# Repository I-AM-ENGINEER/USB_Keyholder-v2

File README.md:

# USB_Keyholder
 Compact USB password manager with battery and oled display

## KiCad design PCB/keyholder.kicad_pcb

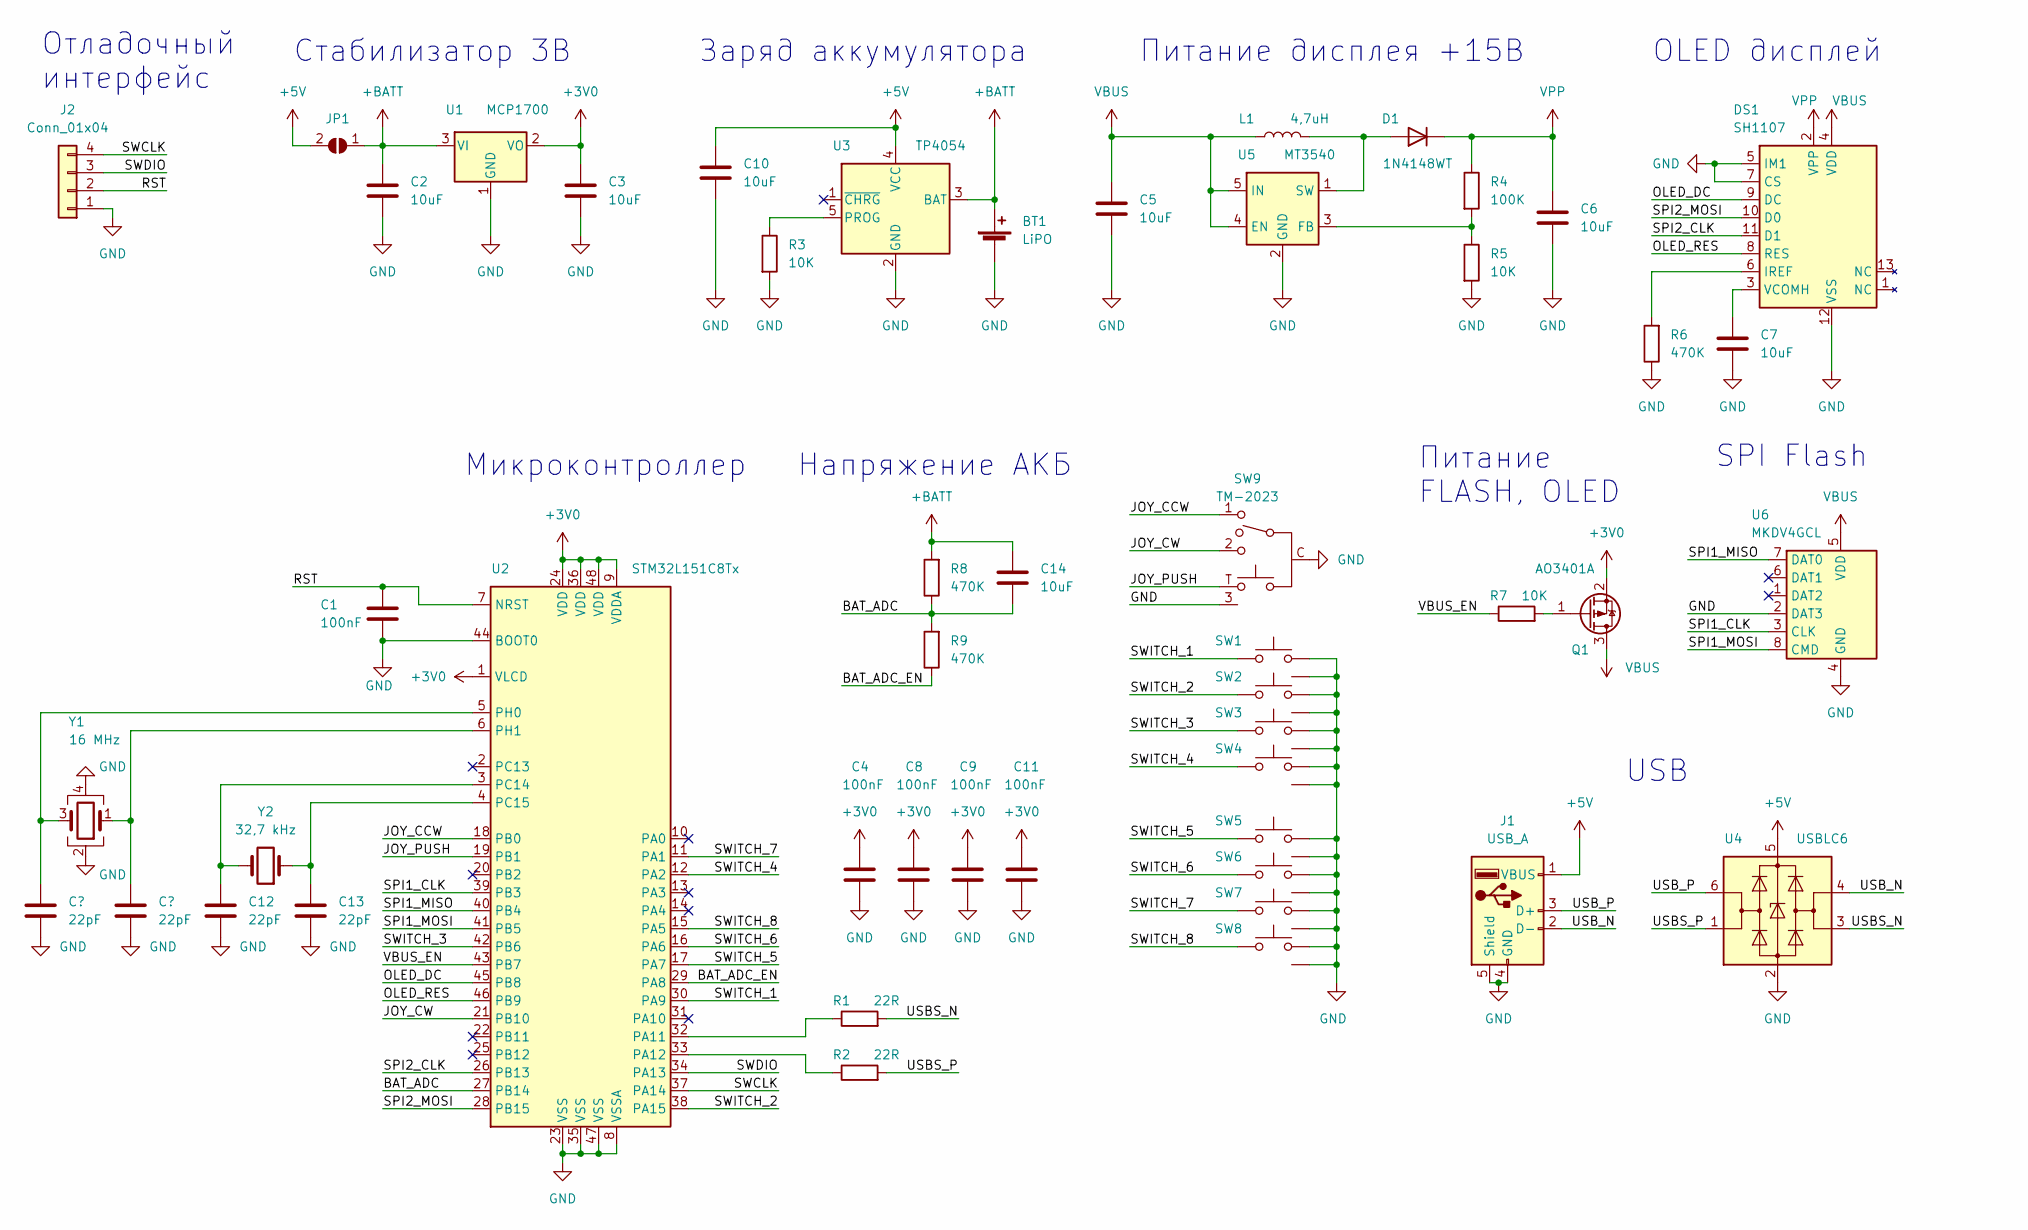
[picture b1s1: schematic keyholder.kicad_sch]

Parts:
BT1: LiPO; PinHeader_1x02_P2.00mm_Vertical
C1, C4, C8, C9, C11: 100nF; C_0603_1608Metric
C2, C3, C5, C6, C7, C10, C14: 10uF; C_0603_1608Metric
C12, C13: 22pF; C_0603_1608Metric
D1: 1N4148WT; D_SOD-523
DS1: SH1107
J1: USB_A; USB_A_CNCTech_1001-011-01101_Horizontal
J2: Conn_01x04; PinHeader_1x04_P1.27mm_Vertical
JP1: SolderJumper_2_Open; SolderJumper-2_P1.3mm_Open_TrianglePad1.0x1.5mm
L1: 4,7uH; L_0603_1608Metric
Q1: AO3401A; SOT-23
R1, R2: 22R; R_0603_1608Metric
R3, R5, R7: 10K; R_0603_1608Metric
R4: 100K; R_0603_1608Metric
R6, R8, R9: 470K; R_0603_1608Metric
SW1, SW2, SW3, SW4, SW5, SW6, SW7, SW8: SW_Push_with_GND; 1TS002G26003500CT
SW9: TM-2023
U1: MCP1700; SOT-23
U2: STM32L151C8Tx; LQFP-48_7x7mm_P0.5mm
U3: TP4054; TSOT-23-5
U4: USBLC6; SOT-23-6
U5: MT3540; SOT-23-6
U6: MKDV4GCL; LGA-8 (8x6)
Y1: 16 MHz; Oscillator_SMD_Abracon_ASE-4Pin_3.2x2.5mm
Y2: 32,7 kHz; Crystal_SMD_EuroQuartz_EQ161-2Pin_3.2x1.5mm

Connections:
+3V0: C3.1, C4.2, C8.2, C9.2, C11.2, Q1.2 (S), U1.2 (VO), U2.1 (VLCD), U2.9 (VDDA), U2.24 (VDD), U2.36 (VDD), U2.48 (VDD)
+5V: C10.1, J1.1 (VBUS), JP1.2 (B), U3.4 (VCC), U4.5 (VBUS)
+BATT: BT1.1 (+), C2.1, C14.2, JP1.1 (A), R8.2, U1.3 (VI), U3.3 (BAT)
/BAT_ADC: C14.1, R8.1, R9.2, U2.27 (PB14)
/BAT_ADC_EN: R9.1, U2.29 (PA8)
/JOY_CCW: SW9.1, U2.18 (PB0)
/JOY_CW: SW9.2, U2.21 (PB10)
/JOY_PUSH: SW9.T, U2.19 (PB1)
/OLED_DC: DS1.9 (DC), U2.45 (PB8)
/OLED_RES: DS1.8 (RES), U2.46 (PB9)
/RST: C1.2, J2.2, U2.7 (NRST)
/SPI1_CLK: U2.39 (PB3), U6.3 (CLK)
/SPI1_MISO: U2.40 (PB4), U6.7 (DAT0)
/SPI1_MOSI: U2.41 (PB5), U6.8 (CMD)
/SPI2_CLK: DS1.11 (D1), U2.26 (PB13)
/SPI2_MOSI: DS1.10 (D0), U2.28 (PB15)
/SWCLK: J2.4, U2.37 (PA14)
/SWDIO: J2.3, U2.34 (PA13)
/SWITCH_1: SW1.1, U2.30 (PA9)
/SWITCH_2: SW2.1, U2.38 (PA15)
/SWITCH_3: SW3.1, U2.42 (PB6)
/SWITCH_4: SW4.1, U2.12 (PA2)
/SWITCH_5: SW5.1, U2.17 (PA7)
/SWITCH_6: SW6.1, U2.16 (PA6)
/SWITCH_7: SW7.1, U2.11 (PA1)
/SWITCH_8: SW8.1, U2.15 (PA5)
/USBS_N: R1.2, U4.3 (I/O2)
/USBS_P: R2.2, U4.1 (I/O1)
/USB_N: J1.2 (D-), U4.4 (I/O2)
/USB_P: J1.3 (D+), U4.6 (I/O1)
/VBUS_EN: R7.1, U2.43 (PB7)
unnamed: C7.1, DS1.3 (VCOMH)
unnamed: C12.1, U2.3 (PC14), Y2.2
unnamed: C13.1, U2.4 (PC15), Y2.1
unnamed: D1.2 (A), L1.2, U5.1 (SW)
unnamed: DS1.6 (IREF), R6.2
unnamed: Q1.1 (G), R7.2
unnamed: R1.1, U2.32 (PA11)
unnamed: R2.1, U2.33 (PA12)
unnamed: R3.1, U3.5 (PROG)
unnamed: R4.2, R5.1, U5.3 (FB)
unnamed: U2.5 (PH0), Y1.3
unnamed: U2.6 (PH1), Y1.1
VBUS: C5.1, DS1.4 (VDD), L1.1, Q1.3 (D), U5.4 (EN), U5.5 (IN), U6.5 (VDD)
VPP: C6.1, D1.1 (K), DS1.2 (VPP), R4.1

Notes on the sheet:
Питание FLASH, OLED
Напряжение АКБ
Отладочный интерфейс
OLED дисплей
Стабилизатор 3В
Микроконтроллер
SPI Flash
Питание дисплея +15В
Заряд аккумулятора
USB

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
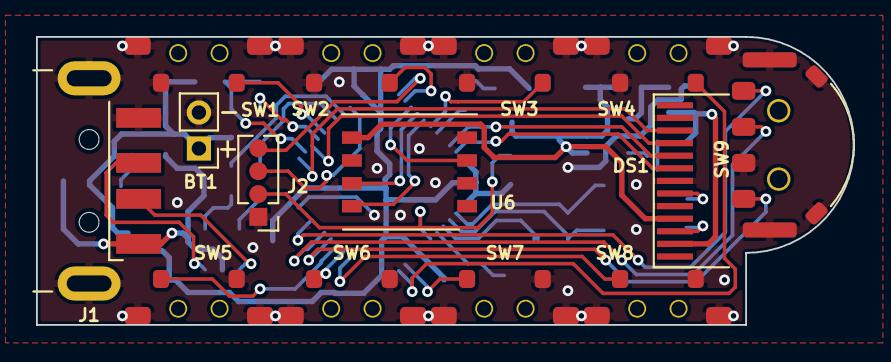
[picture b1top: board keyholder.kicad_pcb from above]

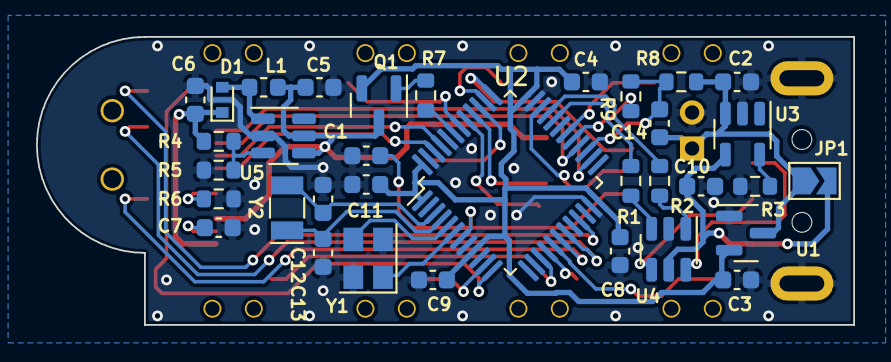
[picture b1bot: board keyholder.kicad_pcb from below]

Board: 2 copper layers, 45.4 x 16.0 mm, 48 parts (34 on the bottom side), 46 nets.

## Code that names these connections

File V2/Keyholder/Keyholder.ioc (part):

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Mcu.Name=STM32L151C(6-8-B)TxA
Mcu.Package=LQFP48
Mcu.UserName=STM32L151C8TxA
PA1.GPIOParameters=GPIO_PuPd,GPIO_Label
PA1.GPIO_Label=SW7
PA1.GPIO_PuPd=GPIO_PULLUP
PA1.Signal=GPIO_Input
PA11.Mode=Device
PA11.Signal=USB_DM
PA12.Mode=Device
PA12.Signal=USB_DP
PA13.Mode=Serial_Wire
PA13.Signal=SYS_JTMS-SWDIO
PA14.Mode=Serial_Wire
PA14.Signal=SYS_JTCK-SWCLK
PA15.GPIOParameters=GPIO_PuPd,GPIO_Label
PA15.GPIO_Label=SW2
PA15.GPIO_PuPd=GPIO_PULLUP
PA15.Signal=GPIO_Input
PA2.GPIOParameters=GPIO_PuPd,GPIO_Label
PA2.GPIO_Label=SW4
PA2.GPIO_PuPd=GPIO_PULLUP
PA2.Signal=GPIO_Input
PA5.GPIOParameters=GPIO_PuPd,GPIO_Label
PA5.GPIO_Label=SW8
PA5.GPIO_PuPd=GPIO_PULLUP
PA5.Signal=GPIO_Input
PA6.GPIOParameters=GPIO_PuPd,GPIO_Label
PA6.GPIO_Label=SW6
PA6.GPIO_PuPd=GPIO_PULLUP
PA6.Signal=GPIO_Input
PA7.GPIOParameters=GPIO_PuPd,GPIO_Label
PA7.GPIO_Label=SW5
PA7.GPIO_PuPd=GPIO_PULLUP
PA7.Signal=GPIO_Input
PA8.GPIOParameters=GPIO_Label
PA8.GPIO_Label=ADC_EN
PA8.Signal=GPIO_Output
PA9.GPIOParameters=GPIO_PuPd,GPIO_Label
PA9.GPIO_Label=SW1
PA9.GPIO_PuPd=GPIO_PULLUP
PA9.Signal=GPIO_Input
PB0.GPIOParameters=GPIO_PuPd,GPIO_Label
PB0.GPIO_Label=JOY_CCW
PB0.GPIO_PuPd=GPIO_PULLUP
PB0.Signal=GPIO_Input
PB1.GPIOParameters=GPIO_PuPd,GPIO_Label
PB1.GPIO_Label=JOY_PUSH
PB1.GPIO_PuPd=GPIO_PULLUP
PB1.Signal=GPIO_Input
PB10.GPIOParameters=GPIO_PuPd,GPIO_Label
PB10.GPIO_Label=JOY_CW
PB10.GPIO_PuPd=GPIO_PULLUP
PB10.Signal=GPIO_Input
PB12.GPIOParameters=GPIO_Label
PB12.GPIO_Label=OLED_CS
PB12.Signal=GPIO_Output
PB13.GPIOParameters=GPIO_Label
PB13.GPIO_Label=OLES_SSPI_MOSI
PB13.Signal=GPIO_Output
PB14.Mode=IN20
PB14.Signal=ADC_IN20
PB15.GPIOParameters=GPIO_Label
PB15.GPIO_Label=OLES_SSPI_SCK
PB15.Signal=GPIO_Output
PB3.Mode=Full_Duplex_Master
PB3.Signal=SPI1_SCK
PB4.Mode=Full_Duplex_Master
PB4.Signal=SPI1_MISO
PB5.Mode=Full_Duplex_Master
PB5.Signal=SPI1_MOSI
PB6.GPIOParameters=GPIO_PuPd,GPIO_Label
PB6.GPIO_Label=SW3
PB6.GPIO_PuPd=GPIO_PULLUP
PB6.Signal=GPIO_Input
PB7.GPIOParameters=GPIO_Label
PB7.GPIO_Label=VBUS_EN
PB7.Signal=GPIO_Output
PB8.GPIOParameters=GPIO_Label
PB8.GPIO_Label=OLED_DC
PB8.Signal=GPIO_Output
PB9.GPIOParameters=GPIO_Label
PB9.GPIO_Label=OLED_RES
PB9.Signal=GPIO_Output
PC14-OSC32_IN.Mode=LSE-External-Oscillator
PC14-OSC32_IN.Signal=RCC_OSC32_IN
PC15-OSC32_OUT.Mode=LSE-External-Oscillator
PC15-OSC32_OUT.Signal=RCC_OSC32_OUT
PH0-OSC_IN.Mode=HSE-External-Oscillator
PH0-OSC_IN.Signal=RCC_OSC_IN
PH1-OSC_OUT.Mode=HSE-External-Oscillator
PH1-OSC_OUT.Signal=RCC_OSC_OUT
RCC.HSE_VALUE=24000000
RCC.SYSCLKFreq_VALUE=24000000
RCC.SYSCLKSource=RCC_SYSCLKSOURCE_HSE
board=custom

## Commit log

2022-02-24 add solidwors model
2022-02-28 Доработка платы + 3д модели
    Добавлены 3Д модели кнопки, аккумулятора, дисплея. Улучшена разводка печатной платы
2022-03-02 3д модели
    Обновлены 3д модели
2022-03-03 Добавлены gerber, обновлена плата, 3Д модель
2022-03-03 Добавил readme для производства
2022-03-08 Обновлен сопроводительный файл производства
2022-03-18 сформировал пакет файлов
2022-03-25 Добавил 3д модели корпуса
2022-04-01 Обновлены STL файлы для сопла 0.5мм
2022-04-13 Добавлен проект cube
2022-04-20 Начата работа с кодом
2022-04-20 Добавлено распознавание кнопок
2022-04-27 Добавлен сон
2022-04-27 добавлено меня входа
2022-04-27 добавлено бета меню
2022-04-27 сделано меню V1.1
2022-04-28 Обновка
2022-05-02 Новые модели
2022-05-02 меню 1.2
2022-05-04 меню v2.0 (beta)
2022-05-05 меню в2.1
2022-05-06 хуевая анимация
2022-05-07 Удалены временные файлы, добавлены иконки
2022-05-07 Настроен USB HID, рефакторинг логики работы вкладок
2022-05-08 Доработан графический интерфейс
2022-05-10 menu pass v1.0
2022-05-10 меню паролей в1.1
    по просьбе великого артема, добавлена функция выхода из режима просмотра паролей. теперь можно не только войти ,но и выйти
2022-05-15 Изменен алгоритм меню на неблокирующий
2022-05-15 Начата работа с USB
2022-05-16 Реализован ввод USB
2022-05-16 меню паролей сделано по человечески
2022-05-18 доработанно меню подпаролей
2022-05-19 Хранение паролей во флеш памяти, запись по UART
2022-05-22 Добавлена PC программа
2022-06-01 Много чего
2022-06-08 движения в питоне
2022-06-09 Update 333.py
    питон не робит нормально
2022-06-11 Работа над 2 версией
2022-06-27 python add
2022-06-27 python что-то исправлено
2022-09-18 Add STP files
2022-09-18 New display now work
2022-09-24 3д доделки
2022-10-01 eще одно изменение корпуса
2022-10-02 ввывыв
2022-10-09 что-то связанное с питоном
2023-03-26 First v2 commit
2023-03-26 Refactor code, start UI hotkeys
2023-03-30 Buggy hotkeys
2023-03-31 Hotkey & usb keyboard fix
2023-04-01 Login menu GUI
2023-12-04 fix crypto_io
2023-12-04 Port to vscode EIDE
2023-12-05 Clean and PC soft upload
2023-12-05 Full vscode ported version
2023-12-06 UI buttons useless function delete, jlink debug
2023-12-06 UI button fix, insert error fix
2023-12-06 Hotkeys bind and delete GUI
2023-12-07 Change IO, storage memory adress
2023-12-07 Keil now compiles
2023-12-07 New login button now work
2023-12-07 Comment set overrun fix
2023-12-07 Save reply fix
2023-12-07 pc soft add hotkey and fix
2023-12-07 Stuck on logins/submenu fix, some ugl changes
2023-12-07 ugl lib dependance fix
2023-12-07 ugl lib dependance fix 2
2023-12-07 Move and scroll now work
2023-12-08 Enter in submenu move random enter fix
2023-12-08 PASSWORD_SET fix
2023-12-09 Now edit +-work
2023-12-10 Password menu fully work
2023-12-12 Battery voltage detection
2023-12-21 FUCKING SLEEP NOW SLEEP 3.1uA!
